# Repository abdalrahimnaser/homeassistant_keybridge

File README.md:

# HASS KeyBridge: Keyboard to Home Assistant MQTT Bridge

## NOTE: there is an updated version of this project with ESPHome support, please refer to the new repo here: https://github.com/abdalrahimnaser/keybridge-esphome

This guide will help you set up your KeyBridge (or your esp32 devkit setup as per `/hardware/devkit_setup`) to convert keyboard and macropad commands into Home Assistant MQTT messages for triggering automations.
Note: make sure that your version of esp32 supports USB Host (ESP32S3 tested working).

## License
This project is licensed for non‑commercial use only. Commercial use is prohibited without prior written permission from the copyright holder. See the LICENSE file for full terms.

## ⭐ Show Your Support!

If you find this project useful, please consider giving it a star! It helps increase the project's visibility and is a great way to show your appreciation. Thank you for your support! 🙏

## Prerequisites

Before getting started, ensure your Home Assistant MQTT configuration is properly set up. For detailed instructions, refer to this tutorial: https://www.youtube.com/watch?v=ImBv2mtaRR0&pp=ygUTaG9tZSBhc3Npc3RhbnQgbXF0dA%3D%3D

## Firmware Setup

### 1. Load the Base Project
In ESP-IDF, load the **HID** example project located under **Host** examples.

### 2. Replace Source Files
Replace all files in the `/main` directory (in the esp idf project) with the files from the `/FW` directory in this repository.

### 3. Configure Network Settings
Run the following command to open the configuration menu:
```bash
idf.py menuconfig
```
Navigate to **Example Connection Configuration** and set:
- Your WiFi network SSID
- Your WiFi password

### 4. Configure MQTT Settings
In `firmware_main.c` (line 56), update the following parameters:
- **MQTT Broker URL**: Replace with your Home Assistant IP and MQTT port (keep the `mqtt://` prefix)
- **MQTT Username**: Set your MQTT broker username
- **MQTT Password**: Set your MQTT broker password

### 5. Build and Flash
Build and flash the project to your ESP32, you can do that in one go via the fire icon in the bottom bar of VS Code (must have the ESP IDF extension set up):

## Home Assistant Automation Setup

### Creating MQTT-Triggered Automations

1. Navigate to **Settings** → **Automations & Scenes** → **Create Automation** → **Create New Automation**

2. **Configure the Trigger ("When" section)**:
   - Search for and select the **MQTT** option
   - Set the **Topic** to: `/keybridge/key`
   - Set the **Payload** to your desired key identifier (e.g., `0` for the zero key)

3. **Configure the Action ("Then Do" section)**:
   - Specify the action to perform when the key is pressed
   - Example: Create a persistent notification for testing purposes

## Example Use Case

A basic automation might trigger a persistent notification whenever the `0` key is pressed on your connected keyboard/macropad, demonstrating successful communication between your KeyBridge and Home Assistant.

You can expand this setup to control lights, switches, scenes, or any other Home Assistant entities based on different key combinations from your input device.

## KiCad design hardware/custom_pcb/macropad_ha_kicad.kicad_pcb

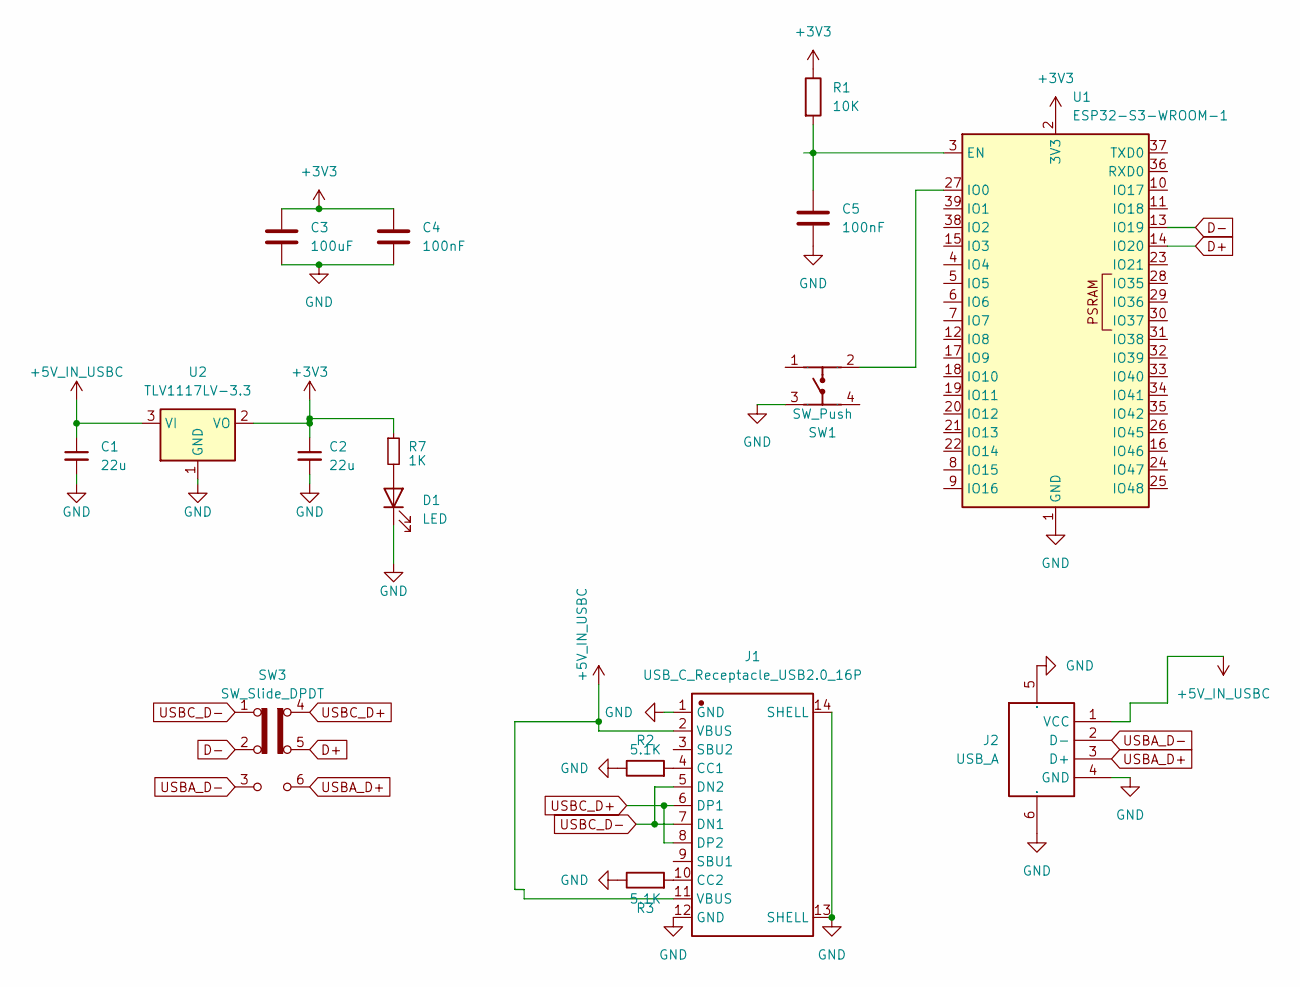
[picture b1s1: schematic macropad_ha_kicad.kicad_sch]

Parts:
C1, C2: 22u; C_0805_2012Metric_Pad1.18x1.45mm_HandSolder
C3: 100uF; C_0805_2012Metric_Pad1.18x1.45mm_HandSolder
C4, C5: 100nF; C_0805_2012Metric_Pad1.18x1.45mm_HandSolder
D1: LED; LED0805-R-RD
J1: USB_C_Receptacle_USB2.0_16P; USB-C-SMD_TYPE-C-6PIN-2MD-073; Manufacturer Part TYPE-C 16PIN 2MD(073)
J2: USB_A; USB-A-SMD_AF180QT1.0; Manufacturer Part AF180QT1.0
R1: 10K; R_0402_1005Metric_Pad0.72x0.64mm_HandSolder
R2, R3: 5.1K; R_0402_1005Metric_Pad0.72x0.64mm_HandSolder
R7: 1K; R_0402_1005Metric_Pad0.72x0.64mm_HandSolder
SW1: SW_Push; SW-SMD_4P-L6.0-W6.0-P4.50-LS9.2; Manufacturer Part TPS645-5NC60
SW3: SW_Slide_DPDT; SW-SMD_6P-L7.2-W3.5-P2.50-LS6.0-TL
U1: ESP32-S3-WROOM-1; WIFIM-SMD_ESP32-S3-WROOM-1-N8
U2: TLV1117LV-3.3; SOT-223-3_TabPin2

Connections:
+3V3: C2.1, C3.1, C4.1, R1.1, R7.1, U1.2 (3V3), U2.2 (VO)
+5V_IN_USBC: C1.1, J1.2 (VBUS), J1.11 (VBUS), J2.1 (VCC), U2.3 (VI)
D+: SW3.5 (B), U1.14 (IO20)
D-: SW3.2 (B), U1.13 (IO19)
GND: C1.2, C2.2, C3.2, C4.2, C5.2, D1.1 (K), J1.1 (GND), J1.12 (GND), J1.13 (SHELL), J1.14 (SHELL), J2.4 (GND), J2.5 (SH1), J2.6 (SH2), R2.1, R3.1, SW1.3, U1.1 (GND), U1.40 (GND), U1.41 (GND), U2.1 (GND)
unnamed: D1.2 (A), R7.2
unnamed: J1.4 (CC1), R2.2
unnamed: J1.10 (CC2), R3.2
unnamed: C5.1, R1.2, U1.3 (EN)
unnamed: SW1.2, U1.27 (IO0)
USBA_D+: J2.3 (D+), SW3.6 (A)
USBA_D-: J2.2 (D-), SW3.3 (C)
USBC_D+: J1.6 (DP1), J1.8 (DP2), SW3.4 (C)
USBC_D-: J1.5 (DN2), J1.7 (DN1), SW3.1 (A)

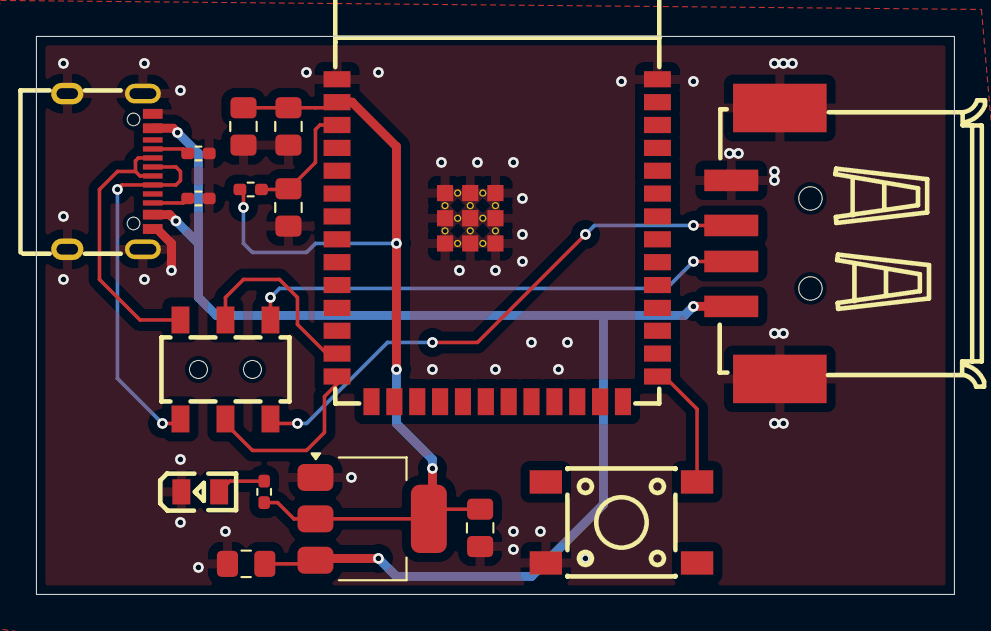
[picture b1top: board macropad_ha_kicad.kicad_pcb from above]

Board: 2 copper layers, 51.0 x 31.0 mm, 16 parts (0 on the bottom side), 14 nets.

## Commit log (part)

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2025-09-05 Added Custom PCB Files
2025-09-05 Rename fabrication-toolkit-options.json to hardware/custom_pcb/fabrication-toolkit-options.json
2025-09-05 Rename finalised_bom.xls to hardware/custom_pcb/finalised_bom.xls
2025-09-05 Rename fp-info-cache to hardware/custom_pcb/fp-info-cache
2025-09-05 Update and rename fp-lib-table to hardware/custom_pcb/fp-lib-table
2025-09-05 Rename gerber.zip to hardware/custom_pcb/gerber.zip
2025-09-05 Rename macropad_ha_kicad.kicad_prl to hardware/custom_pcb/macropad_ha_kicad.kicad_prl
2025-09-05 Rename macropad_ha_kicad.kicad_pro to hardware/custom_pcb/macropad_ha_kicad.kicad_pro
2025-09-05 Update and rename macropad_ha_kicad.kicad_sch-bak to hardware/custom_pcb/macropad_ha_kicad.kicad_sch-bak
2025-09-05 added schematic for devkit setup
2025-09-05 refactor
2025-09-06 rename to FW
2025-09-10 Create LICENSE
